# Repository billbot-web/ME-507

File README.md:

# SportTrackr: Camera-Guided Dual-Axis Tracking System

An ESP32-based real-time tracking system that combines computer vision, motion control, and web telemetry to automatically track LED targets using a camera-guided pan-tilt mechanism.

## Project Overview

SportTrackr is an embedded control system designed for automated visual tracking applications. The system uses an OV5640 camera module for target detection, dual DC motors with encoders for precise pan-tilt control, and an IMU for orientation sensing. All components are coordinated through a FreeRTOS-based task architecture with PID control loops for smooth and accurate tracking.

### Key Features

- **Autonomous LED Tracking**: Real-time computer vision processing for target detection and tracking
- **Multi-Mode Operation**: Automatic tracking, manual control, velocity mode, and position mode
- **Web Interface**: Live telemetry streaming and remote control via WiFi
- **Precision Control**: Closed-loop PID control with encoder feedback
- **Sensor Fusion**: 9-DOF IMU integration for enhanced stability
- **Modular Architecture**: FSM-based task design for easy extension and debugging

## 📁 Repository Structure

```
├── data/              # Web UI assets (HTML, CSS, JavaScript)
├── docs/              # Doxygen-generated documentation
├── src/               # Source code
│   ├── hardware/      # Hardware drivers (motors, encoders, camera, IMU)
│   ├── tasks/         # FreeRTOS task implementations
│   ├── fsm/           # Finite state machine framework
│   └── main.cpp       # System initialization and setup
└── hardware/          # Physical design files
    ├── cad/           # Mechanical CAD files (SolidWorks)
    └── pcb/           # PCB design files (KiCad)
```

## System Components

### Hardware
- **MCU**: ESP32-WROVER (Dual-core, WiFi, 4MB PSRAM)
- **Camera**: OV5640 (5MP, autofocus, JPEG compression)
- **Motors**: 2× DC motors with 70:1 gearboxes
- **Drivers**: 2× DRV8833 dual H-bridge motor controllers
- **Encoders**: 2× Quadrature encoders (64 CPR)
- **IMU**: BNO055 (9-DOF: accelerometer, gyroscope, magnetometer)

### Software Stack
- **Framework**: Arduino/ESP-IDF on PlatformIO
- **RTOS**: FreeRTOS for multitasking
- **Web Server**: ESPAsyncWebServer for WiFi interface
- **Control**: Custom PID implementation with multiple tuning profiles

## Documentation

Detailed documentation is available for each subsystem:

- **[Mechanical Design](hardware/cad/README.md)** - CAD models, assemblies, and 3D-printed parts
- **[Electronic Design](hardware/pcb/README.md)** - PCB schematics, board layout, and wiring
- **[Software Architecture](src/README.md)** - Code organization and design patterns
  - [Hardware Drivers](src/hardware/README.md) - Low-level peripheral interfaces
  - [Task Controllers](src/tasks/README.md) - FreeRTOS task implementations
  - [FSM Framework](src/fsm/README.md) - State machine design pattern
- **[Web Interface](data/README.md)** - User interface and telemetry system
- **[API Reference](docs/html/index.html)** - Full Doxygen documentation

## Getting Started

### Prerequisites
- PlatformIO IDE (VS Code extension recommended)
- ESP32 toolchain
- USB-to-Serial driver for ESP32

### Build and Upload
```bash
# Clone the repository
git clone https://github.com/billbot-web/ME-507.git
cd ME-507

# Build the project
pio run

# Upload to ESP32
pio run --target upload

# Upload filesystem (web UI)
pio run --target uploadfs

# Monitor serial output
pio device monitor
```

### Configuration
1. Update WiFi credentials in `src/tasks/UITask.cpp`
2. Adjust PID tuning parameters in `src/main.cpp` (see comments for guidance)
3. Calibrate camera detection thresholds in `src/tasks/CameraTask.cpp`

## Operating Modes

The system supports four distinct operating modes:

1. **TRACKER**: Autonomous camera-based target tracking with PID control
2. **TELEOP**: Manual velocity control via web interface
3. **MOTOR_TEST**: Open-loop motor testing for diagnostics
4. **CALIBRATE**: Encoder homing and reference position setup

Modes are switched via the web interface or programmatically through the ControllerTask.

## System Architecture

The system uses a modular FreeRTOS task architecture:

- **MotorTask** (2 instances): Multi-mode motor control with FSM-based state management
- **EncoderTask** (2 instances): High-frequency position/velocity measurement using ESP32 PCNT
- **ControllerTask**: System coordinator and mode manager
- **CameraTask**: Computer vision processing for LED detection
- **IMUTask**: Orientation sensing and sensor data fusion
- **UITask**: Web server, telemetry streaming, and user commands

Tasks communicate via FreeRTOS queues and share data through thread-safe mechanisms.

## Performance

- **Control Loop Rate**: 100 Hz (10ms task periods)
- **Camera Frame Rate**: ~10-15 FPS (JPEG compression)
- **Encoder Resolution**: 4480 counts/revolution (with gearbox)
- **Position Accuracy**: ±0.5° typical
- **Latency**: <50ms from detection to motor response

## Contributors

- **Johnny Rourke** - Software, Integration, Mechanical Design & CAD
- **William Hawkins** - Software, Electronics & PCB Design

## License

This project was developed as part of ME 507 (Mechatronics) at California Polytechnic State University, San Luis Obispo.

## 🔗 Additional Resources

- [Doxygen Documentation](docs/html/index.html) - Complete API reference
- [FSM Design Pattern](src/fsm/FSM.md) - State machine implementation details
- [PID Tuning Guide](src/main.cpp) - Controller configuration instructions

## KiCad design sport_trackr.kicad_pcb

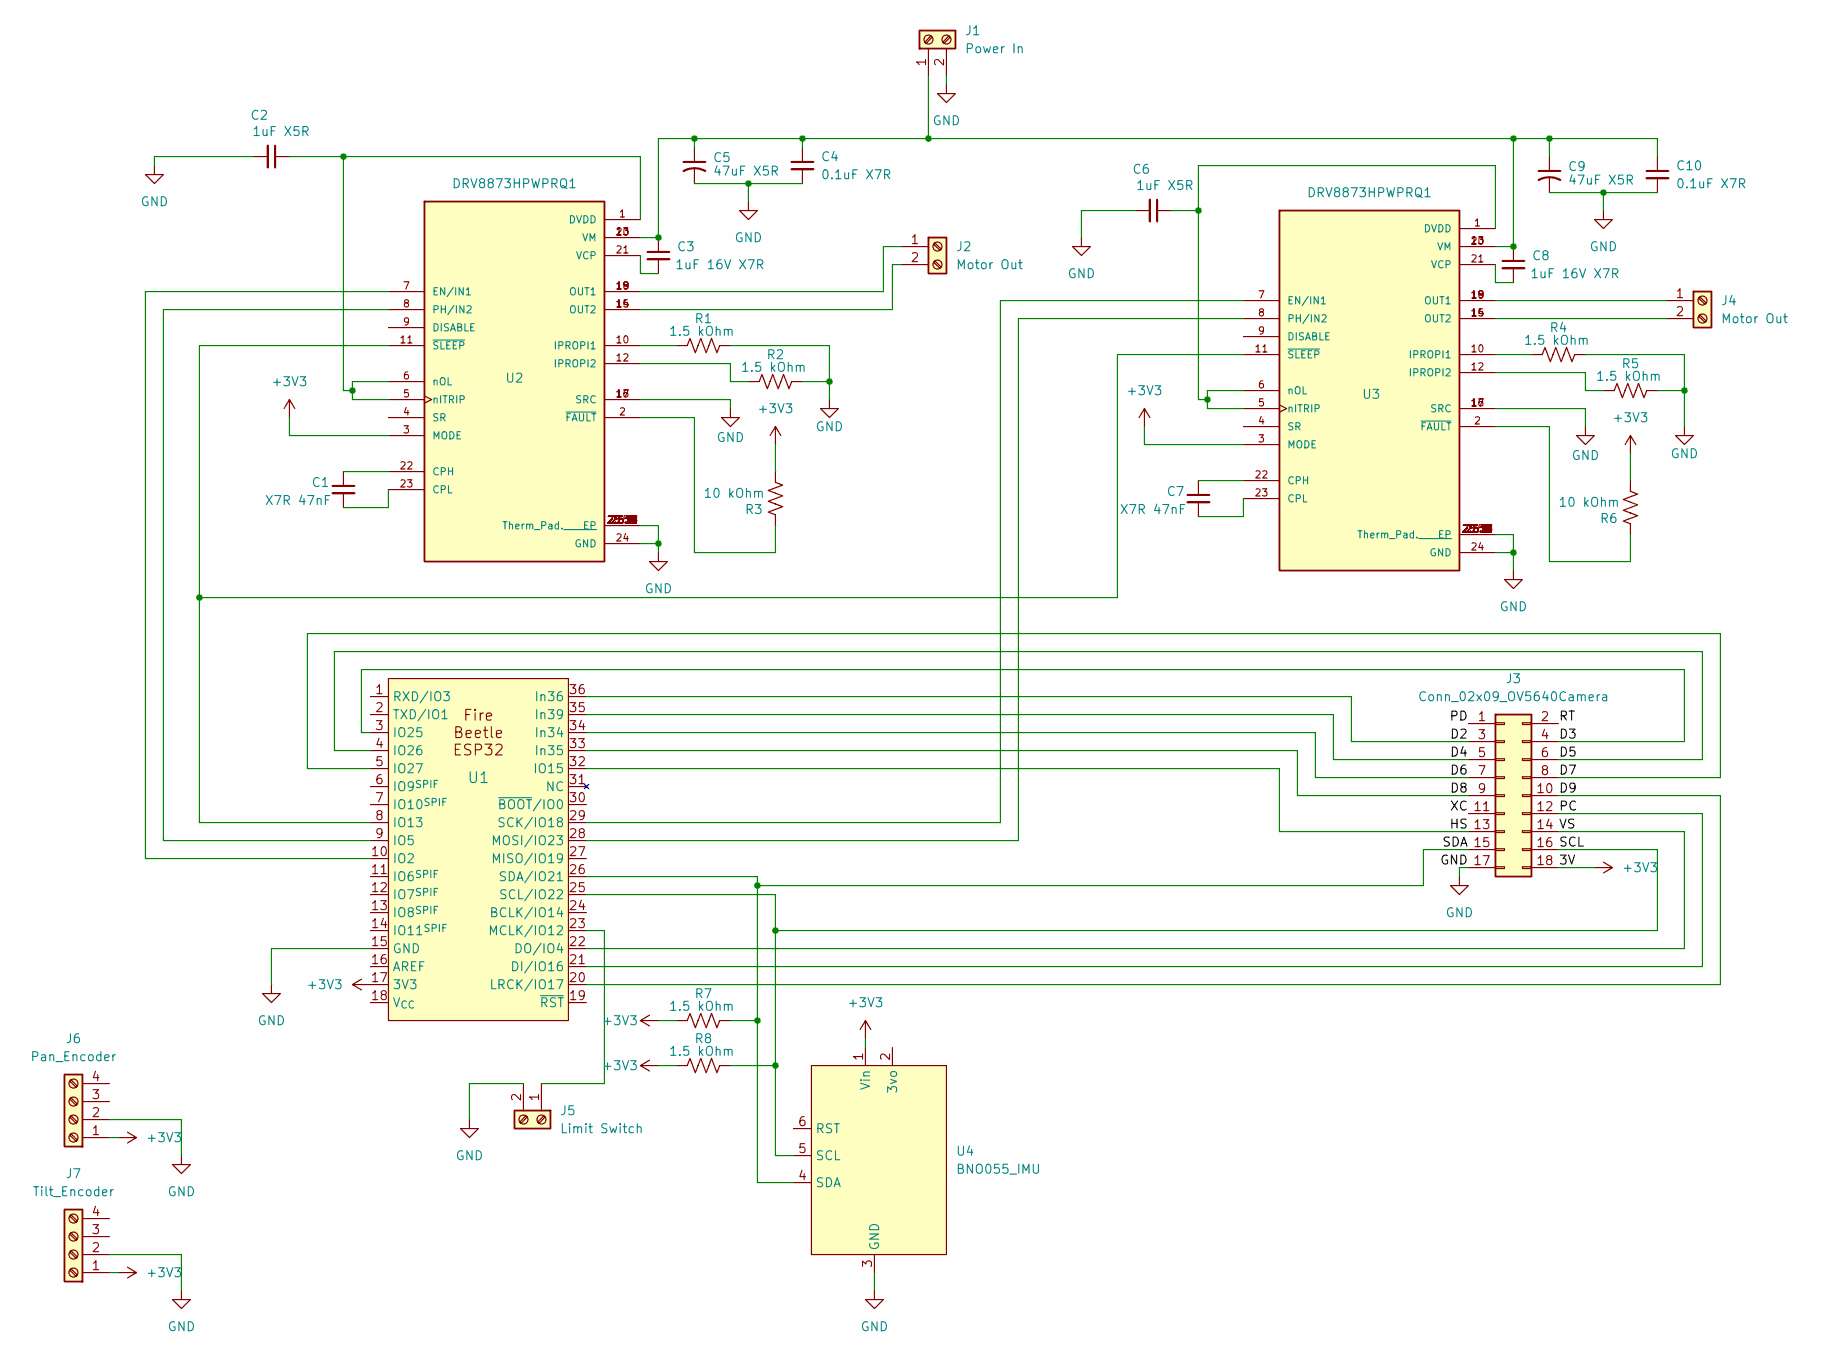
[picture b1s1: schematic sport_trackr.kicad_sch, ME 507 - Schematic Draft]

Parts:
C1, C7: X7R 47nF; C_0805_2012Metric_Pad1.18x1.45mm_HandSolder
C2, C6: 1uF X5R; C_0805_2012Metric_Pad1.18x1.45mm_HandSolder
C3, C8: 1uF 16V X7R; C_0805_2012Metric_Pad1.18x1.45mm_HandSolder
C4, C10: 0.1uF X7R; C_0805_2012Metric_Pad1.18x1.45mm_HandSolder
C5, C9: 47uF X5R; C_1206_3216Metric_Pad1.33x1.80mm_HandSolder
J1: Power In; TerminalBlock_Phoenix_MKDS-1,5-2_1x02_P5.00mm_Horizontal
J2, J4: Motor Out; TerminalBlock_Phoenix_MKDS-1,5-2_1x02_P5.00mm_Horizontal
J3: Conn_02x09_OV5640Camera; PinHeader_2x09_P2.54mm_Vertical
J5: Limit Switch; TerminalBlock_Phoenix_MPT-0,5-2-2.54_1x02_P2.54mm_Horizontal
J6: Pan_Encoder; PinHeader_1x04_P2.54mm_Vertical
J7: Tilt_Encoder; PinHeader_1x04_P2.54mm_Vertical
R1, R2, R4, R5, R7, R8: 1.5 kOhm; R_0805_2012Metric_Pad1.20x1.40mm_HandSolder
R3, R6: 10 kOhm; R_0805_2012Metric_Pad1.20x1.40mm_HandSolder
U1: FireBeetle-ESP32
U2, U3: DRV8873HPWPRQ1; IC_DRV8873SPWPRQ1; PARTREV A
U4: BNO055_IMU; PinHeader_1x06_P2.54mm_Vertical

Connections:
+3V3: J3.18, J6.1, J7.1, R3.2, R6.2, R7.1, R8.1, U1.17 (3V3), U2.3 (MODE), U3.3 (MODE), U4.1 (Vin)
/D2: J3.3, U1.36 (In36)
/D3: J3.4, U1.3 (IO25)
/D4: J3.5, U1.35 (In39)
/D5: J3.6, U1.4 (IO26)
/D6: J3.7, U1.34 (In34)
/D7: J3.8, U1.5 (IO27)
/D8: J3.9, U1.33 (In35)
/D9: J3.10, U1.20 (LRCK/IO17)
/HS: J3.13, U1.32 (IO15)
/PC: J3.12, U1.21 (DI/IO16)
/PD: J3.1
/RT: J3.2
/SCL: J3.16, R8.2, U1.25 (SCL/IO22), U4.5 (SCL)
/SDA: J3.15, R7.2, U1.26 (SDA/IO21), U4.4 (SDA)
/VS: J3.14, U1.22 (DO/IO4)
/XC: J3.11
GND: C2.2, C4.2, C5.2, C6.2, C9.2, C10.2, J1.2, J3.17, J5.2, J6.2, J7.2, R1.2, R2.2, R4.2, R5.2, U1.15 (GND), U2.16 (SRC), U2.17 (SRC), U2.24 (GND), U2.25 (Therm_Pad.______), U2.25.1 (EP), U2.25.2 (EP), U2.25.3 (EP), U2.25.4 (EP), U2.25.5 (EP), U2.25.6 (EP), U2.25.7 (EP), U2.25.8 (EP), U2.25.9 (EP), U2.25.10 (EP), U2.25.11 (EP), U2.25.12 (EP), U2.25.13 (EP), U2.25.14 (EP), U2.25.15 (EP), U2.25.16 (EP), U2.25.17 (EP), U2.25.18 (EP), U3.16 (SRC), U3.17 (SRC), U3.24 (GND), U3.25 (Therm_Pad.______), U3.25.1 (EP), U3.25.2 (EP), U3.25.3 (EP), U3.25.4 (EP), U3.25.5 (EP), U3.25.6 (EP), U3.25.7 (EP), U3.25.8 (EP), U3.25.9 (EP), U3.25.10 (EP), U3.25.11 (EP), U3.25.12 (EP), U3.25.13 (EP), U3.25.14 (EP), U3.25.15 (EP), U3.25.16 (EP), U3.25.17 (EP), U3.25.18 (EP), U4.3 (GND)
unnamed: C3.1, C4.1, C5.1, C8.1, C9.1, C10.1, J1.1, U2.13 (VM), U2.20 (VM), U3.13 (VM), U3.20 (VM)
unnamed: J2.1, U2.18 (OUT1), U2.19 (OUT1)
unnamed: J2.2, U2.14 (OUT2), U2.15 (OUT2)
unnamed: J4.1, U3.18 (OUT1), U3.19 (OUT1)
unnamed: J4.2, U3.14 (OUT2), U3.15 (OUT2)
unnamed: J5.1, U1.23 (MCLK/IO12)
unnamed: U1.10 (IO2), U2.7 (EN/IN1)
unnamed: U1.9 (IO5), U2.8 (PH/IN2)
unnamed: U1.8 (IO13), U2.11 (~SLEEP), U3.11 (~SLEEP)
unnamed: U1.28 (MOSI/IO23), U3.8 (PH/IN2)
unnamed: U1.29 (SCK/IO18), U3.7 (EN/IN1)
unnamed: C1.1, U2.22 (CPH)
unnamed: C1.2, U2.23 (CPL)
unnamed: C2.1, U2.1 (DVDD), U2.5 (nITRIP), U2.6 (nOL)
unnamed: R1.1, U2.10 (IPROPI1)
unnamed: R2.1, U2.12 (IPROPI2)
unnamed: C3.2, U2.21 (VCP)
unnamed: R3.1, U2.2 (~FAULT)
unnamed: C7.1, U3.22 (CPH)
unnamed: C7.2, U3.23 (CPL)
unnamed: C6.1, U3.1 (DVDD), U3.5 (nITRIP), U3.6 (nOL)
unnamed: R4.1, U3.10 (IPROPI1)
unnamed: R5.1, U3.12 (IPROPI2)
unnamed: C8.2, U3.21 (VCP)
unnamed: R6.1, U3.2 (~FAULT)

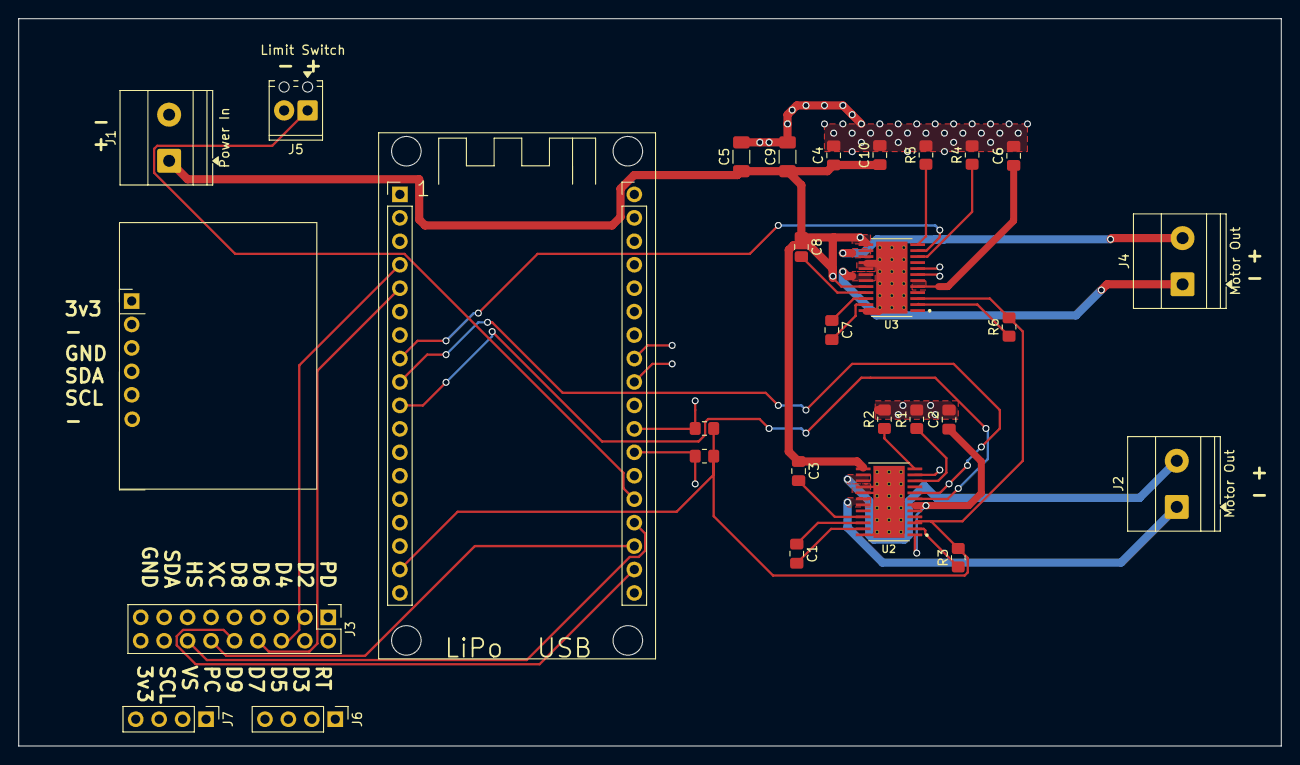
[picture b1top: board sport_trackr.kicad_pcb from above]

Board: 4 copper layers, 136.8 x 78.8 mm, 29 parts (0 on the bottom side), 40 nets.

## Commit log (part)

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2025-10-16 Getting started reading images from ESP32
    This guide provides step-by-step instructions for setting up the ESP32-S3 + OV5640 camera project, including software installation, project setup, and troubleshooting common issues.
2025-10-16 Revise README for ME 507 project details
    Updated README to include project directory information.
2025-10-31 Add files via upload
    Newest version of PCB and schematic
2025-11-07 initial commit motorencoder
2025-11-07 Update FSM and README docs
2025-11-07 Update FSM implementation and docs
2025-11-13 Initial commit: MotorEncoderUI PlatformIO project with encoder, motor, and UI tasks
2025-11-14 Implement position control with PID and fix command conflicts
    Major changes:
    - Add PID controllers to MotorTask for velocity and position control
    - Implement position control state machine in MotorTask
    - Convert position data type from int32_t to float throughout codebase
    - Fix encoder overflow detection and add GPIO pull-ups
    - Add two-step UI (mode selection then value input) in UITask
2025-11-14 Add README file for hardware subdirectory
2025-11-14 Added final board design schematic and pcb files
2025-11-21 Add comprehensive Doxygen documentation and BNO055 IMU integration
    Major improvements:
    - Added detailed Doxygen documentation throughout all source files
    - Integrated BNO055 IMU sensor with FSM-based task architecture
    - Added real-time IMU telemetry to web interface (Euler angles, gyroscope, accelerometer)
    - Converted IMU data sharing from arrays to structs for Share<T> compatibility
    - Enhanced web interface with separated HTML/CSS/JS files for maintainability
2025-11-24 Added camera support with OV5640 Class and CameraTask files
2025-11-25 Added PID controller task for camera following
2025-11-25 duplicated motor and encoder objects to implement both tilt and pan control
2025-12-01 "Major changes to the ui task implemented the full ui with the trackr and teleop modes"
2025-12-01 print statements indicating entry into CALIBRATE a nd MOTOR_TEST states
2025-12-02 making it work
2025-12-02 debuggggging
2025-12-09 Organizing for the repository 'motor-encoder-ui'
2025-12-09 made the doxygen files
2025-12-09 Restructuring the project directories and updating include paths accordingly
2025-12-09 organizing the repo moving the pcb into main
2025-12-09 Changing the cad files directory structure to be more organized
2025-12-09 get rid of the fiels in gitignore
2025-12-09 moved pcb files into the pcb folder
2025-12-09 finished adding file: .git/COMMIT_EDITMSG
2025-12-09 added all the readmes
2025-12-09 Fix image tag syntax in hardware README
    Updated image tag in README to correct HTML syntax.
2025-12-09 Add link to Adafruit BNO055 driver in README
    Updated the README to include a link for the Adafruit BNO055 driver.
2025-12-10 Revise motor usage examples and formatting
    Updated usage examples and corrected text formatting.
2025-12-10 Rename setEff method to set_eff for consistency
2025-12-10 Update README.md for formatting and section titles
2025-12-10 have doxy files
2025-12-10 Add task diagram to README
    Added task diagram to the README for better understanding.
2025-12-13 Enhance README with task overview images
    Added images to various task overviews in README.
2026-04-24 Update project title to 'Dual-Axis Tracking System'
